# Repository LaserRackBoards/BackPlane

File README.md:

# BackPlane
19" 3U 84HP backplane used with Schroff subracks (might work with other brands also)

Fits 10pcs boards with 8HP front-panels and one board with 4HP panel (rightmost).

* connector: DIN41612, type C, 64 pins in rows a+c
* +15V/GND/-15V supply shared between all boards
* 17+17pin bus shared between all boards
* 2pins board-specific, all routed to slot-1 (J1, leftmost)

Backplane connector, Digikey 1195-1175-ND, Harting 09032646824, https://b2b.harting.com/09032646824

PCB RA connector, Digikey 1195-1149-ND, Harting 09031646921, https://b2b.harting.com/09036642921

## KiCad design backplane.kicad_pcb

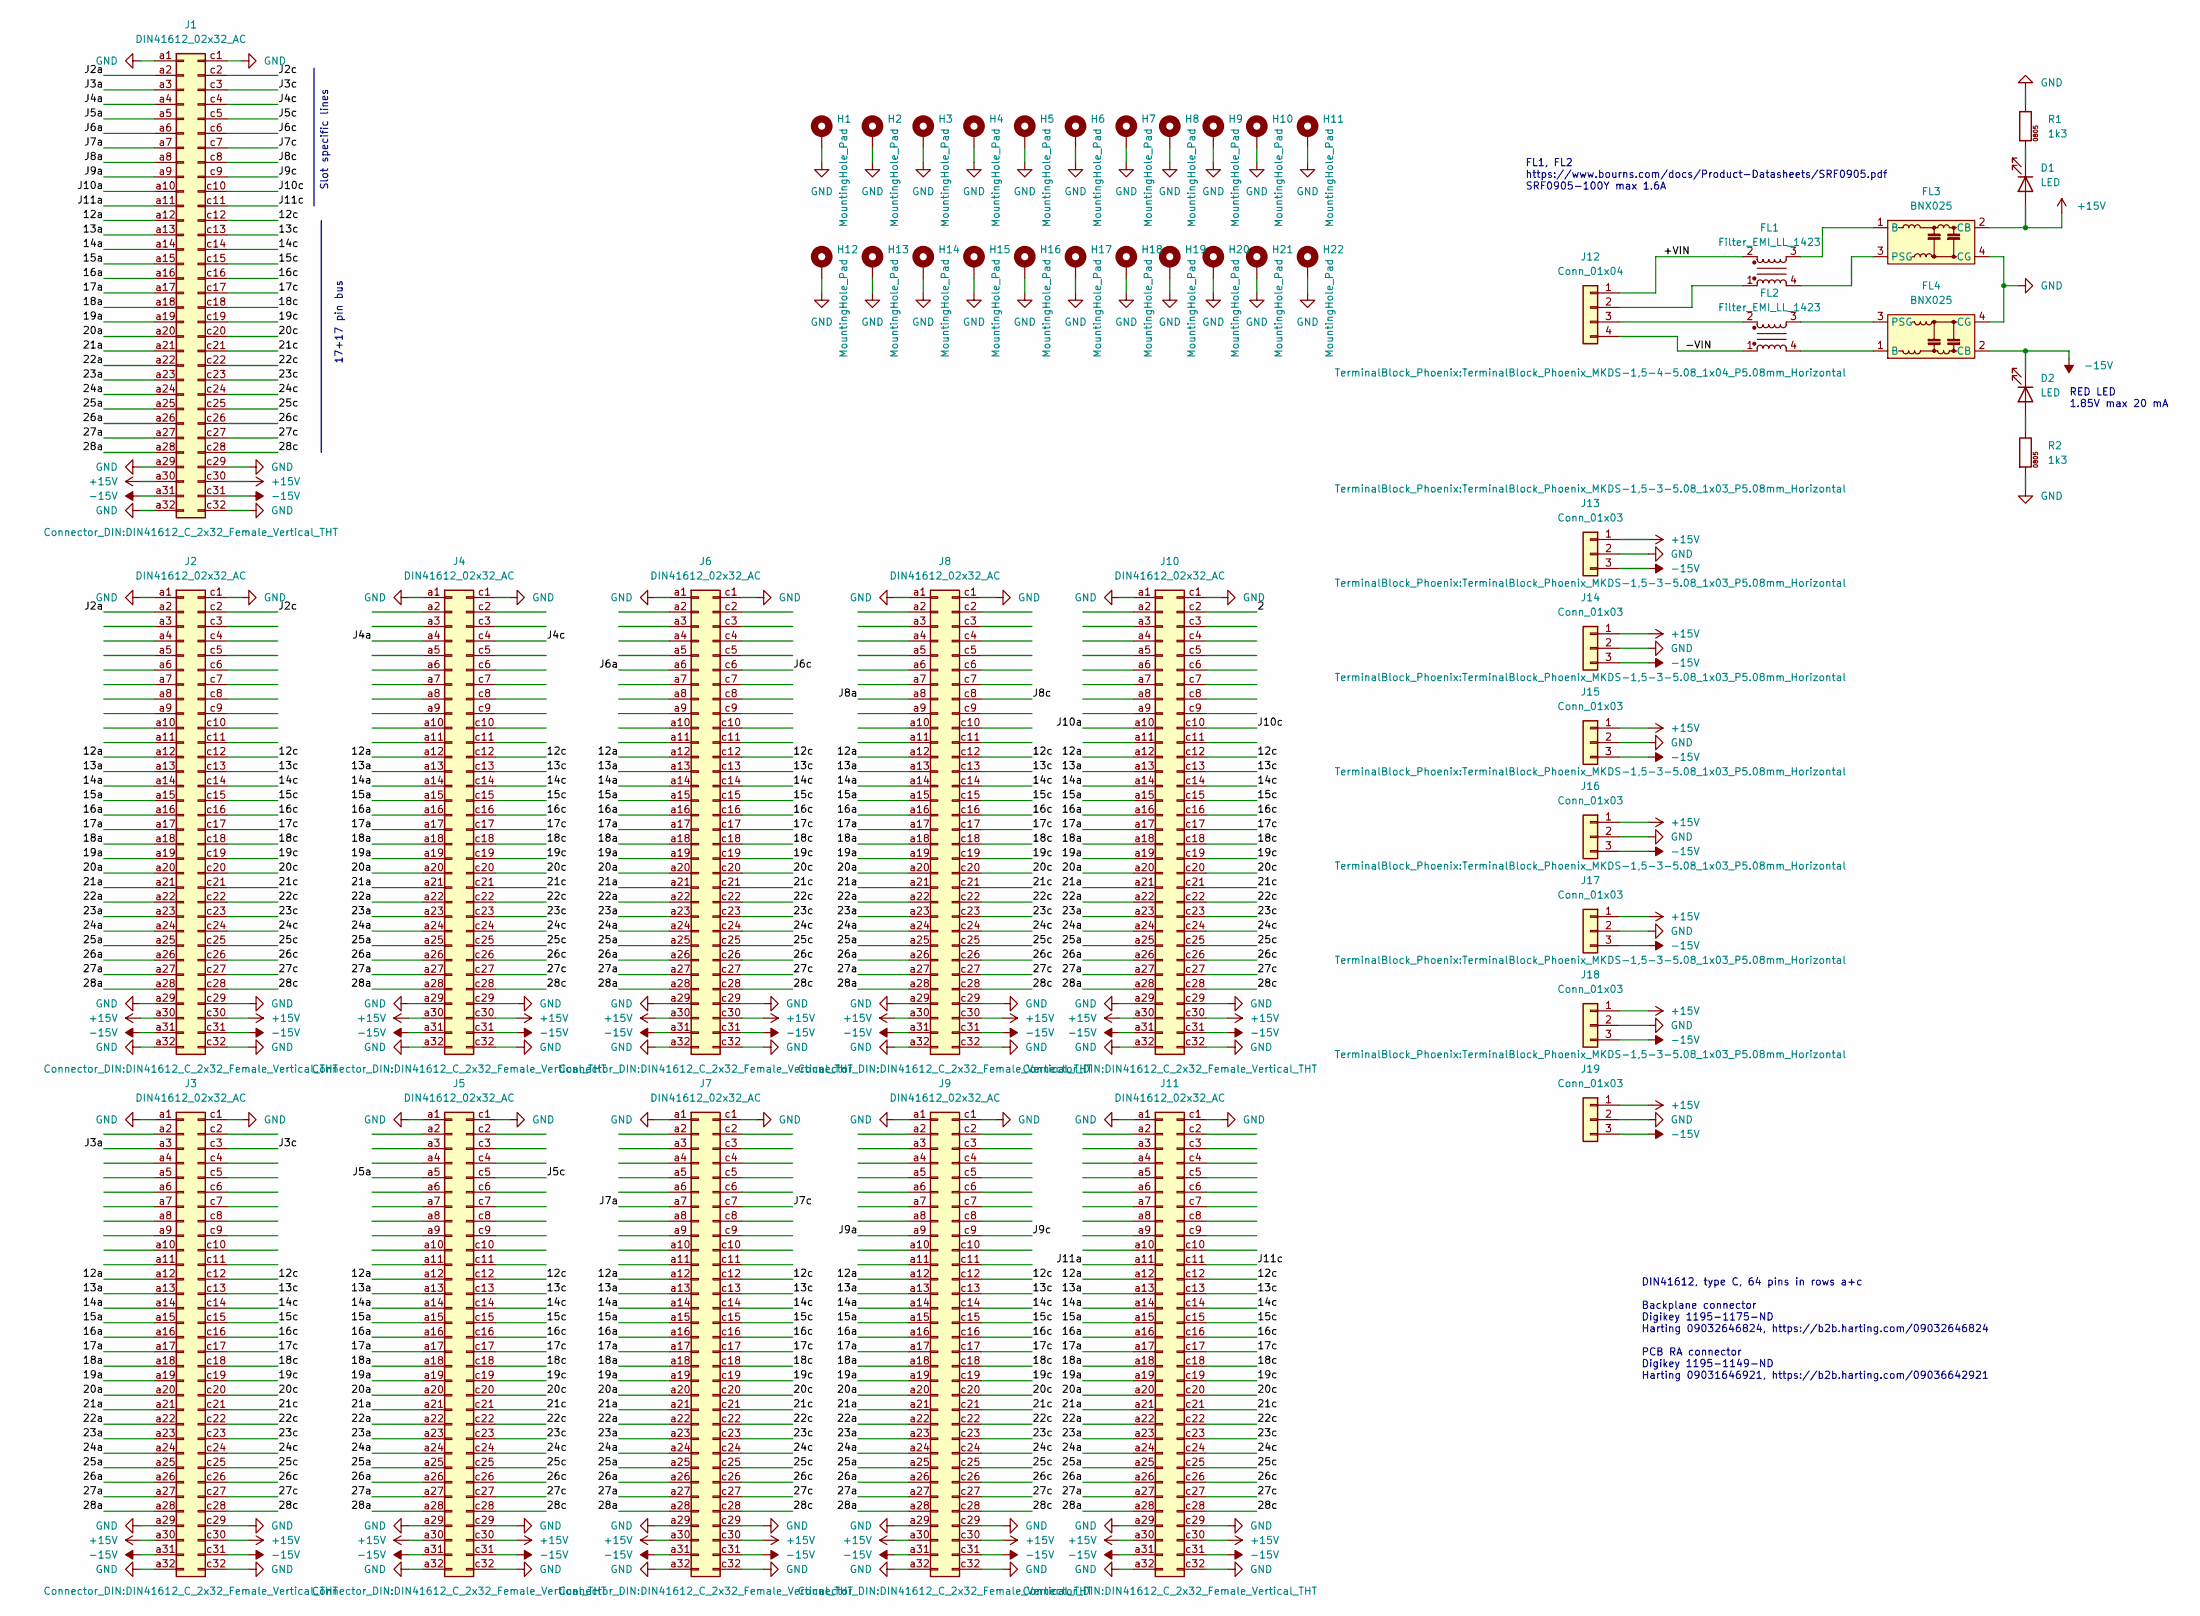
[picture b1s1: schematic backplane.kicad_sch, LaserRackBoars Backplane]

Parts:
D1, D2: LED; LED_0805_2012Metric
FL1, FL2: Filter_EMI_LL_1423; Filter_Bourns_SRF0905_6.0x9.2mm
FL3, FL4: BNX025; Filter_Murata_BNX025
H1, H2, H3, H4, H5, H6, H7, H8, H9, H10, H11, H12, H13, H14, H15, H16, H17, H18, H19, H20, H21, H22: MountingHole_Pad; MountingHole_2.7mm_M2.5_DIN965
J1, J2, J3, J4, J5, J6, J7, J8, J9, J10, J11: DIN41612_02x32_AC; DIN41612_C_2x32_Female_Vertical_THT
J12: Conn_01x04; TerminalBlock_Phoenix_MKDS-1,5-4-5.08_1x04_P5.08mm_Horizont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
J13, J14, J15, J16, J17, J18, J19: Conn_01x03; TerminalBlock_Phoenix_MKDS-1,5-3-5.08_1x03_P5.08mm_Horizont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
R1, R2: 1k3; R_0805_2012Metric

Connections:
+15V: D1.2 (A), FL3.2 (CB), J1.a30, J1.c30, J2.a30, J2.c30, J3.a30, J3.c30, J4.a30, J4.c30, J5.a30, J5.c30, J6.a30, J6.c30, J7.a30, J7.c30, J8.a30, J8.c30, J9.a30, J9.c30, J10.a30, J10.c30, J11.a30, J11.c30, J13.1, J14.1, J15.1, J16.1, J17.1, J18.1, J19.1
-15V: D2.1 (K), FL4.2 (CB), J1.a31, J1.c31, J2.a31, J2.c31, J3.a31, J3.c31, J4.a31, J4.c31, J5.a31, J5.c31, J6.a31, J6.c31, J7.a31, J7.c31, J8.a31, J8.c31, J9.a31, J9.c31, J10.a31, J10.c31, J11.a31, J11.c31, J13.3, J14.3, J15.3, J16.3, J17.3, J18.3, J19.3
/2: J10.c2
/12a: J1.a12, J2.a12, J3.a12, J4.a12, J5.a12, J6.a12, J7.a12, J8.a12, J9.a12, J10.a12, J11.a12
/12c: J1.c12, J2.c12, J3.c12, J4.c12, J5.c12, J6.c12, J7.c12, J8.c12, J9.c12, J10.c12, J11.c12
/13a: J1.a13, J2.a13, J3.a13, J4.a13, J5.a13, J6.a13, J7.a13, J8.a13, J9.a13, J10.a13, J11.a13
/13c: J1.c13, J2.c13, J3.c13, J4.c13, J5.c13, J6.c13, J7.c13, J8.c13, J9.c13, J10.c13, J11.c13
/14a: J1.a14, J2.a14, J3.a14, J4.a14, J5.a14, J6.a14, J7.a14, J8.a14, J9.a14, J10.a14, J11.a14
/14c: J1.c14, J2.c14, J3.c14, J4.c14, J5.c14, J6.c14, J7.c14, J8.c14, J9.c14, J10.c14, J11.c14
/15a: J1.a15, J2.a15, J3.a15, J4.a15, J5.a15, J6.a15, J7.a15, J8.a15, J9.a15, J10.a15, J11.a15
/15c: J1.c15, J2.c15, J3.c15, J4.c15, J5.c15, J6.c15, J7.c15, J8.c15, J9.c15, J10.c15, J11.c15
/16a: J1.a16, J2.a16, J3.a16, J4.a16, J5.a16, J6.a16, J7.a16, J8.a16, J9.a16, J10.a16, J11.a16
/16c: J1.c16, J2.c16, J3.c16, J4.c16, J5.c16, J6.c16, J7.c16, J8.c16, J9.c16, J10.c16, J11.c16
/17a: J1.a17, J2.a17, J3.a17, J4.a17, J5.a17, J6.a17, J7.a17, J8.a17, J9.a17, J10.a17, J11.a17
/17c: J1.c17, J2.c17, J3.c17, J4.c17, J5.c17, J6.c17, J7.c17, J8.c17, J9.c17, J10.c17, J11.c17
/18a: J1.a18, J2.a18, J3.a18, J4.a18, J5.a18, J6.a18, J7.a18, J8.a18, J9.a18, J10.a18, J11.a18
/18c: J1.c18, J2.c18, J3.c18, J4.c18, J5.c18, J6.c18, J7.c18, J8.c18, J9.c18, J10.c18, J11.c18
/19a: J1.a19, J2.a19, J3.a19, J4.a19, J5.a19, J6.a19, J7.a19, J8.a19, J9.a19, J10.a19, J11.a19
/19c: J1.c19, J2.c19, J3.c19, J4.c19, J5.c19, J6.c19, J7.c19, J8.c19, J9.c19, J10.c19, J11.c19
/20a: J1.a20, J2.a20, J3.a20, J4.a20, J5.a20, J6.a20, J7.a20, J8.a20, J9.a20, J10.a20, J11.a20
/20c: J1.c20, J2.c20, J3.c20, J4.c20, J5.c20, J6.c20, J7.c20, J8.c20, J9.c20, J10.c20, J11.c20
/21a: J1.a21, J2.a21, J3.a21, J4.a21, J5.a21, J6.a21, J7.a21, J8.a21, J9.a21, J10.a21, J11.a21
/21c: J1.c21, J2.c21, J3.c21, J4.c21, J5.c21, J6.c21, J7.c21, J8.c21, J9.c21, J10.c21, J11.c21
/22a: J1.a22, J2.a22, J3.a22, J4.a22, J5.a22, J6.a22, J7.a22, J8.a22, J9.a22, J10.a22, J11.a22
/22c: J1.c22, J2.c22, J3.c22, J4.c22, J5.c22, J6.c22, J7.c22, J8.c22, J9.c22, J10.c22, J11.c22
/23a: J1.a23, J2.a23, J3.a23, J4.a23, J5.a23, J6.a23, J7.a23, J8.a23, J9.a23, J10.a23, J11.a23
/23c: J1.c23, J2.c23, J3.c23, J4.c23, J5.c23, J6.c23, J7.c23, J8.c23, J9.c23, J10.c23, J11.c23
/24a: J1.a24, J2.a24, J3.a24, J4.a24, J5.a24, J6.a24, J7.a24, J8.a24, J9.a24, J10.a24, J11.a24
/24c: J1.c24, J2.c24, J3.c24, J4.c24, J5.c24, J6.c24, J7.c24, J8.c24, J9.c24, J10.c24, J11.c24
/25a: J1.a25, J2.a25, J3.a25, J4.a25, J5.a25, J6.a25, J7.a25, J8.a25, J9.a25, J10.a25, J11.a25
/25c: J1.c25, J2.c25, J3.c25, J4.c25, J5.c25, J6.c25, J7.c25, J8.c25, J9.c25, J10.c25, J11.c25
/26a: J1.a26, J2.a26, J3.a26, J4.a26, J5.a26, J6.a26, J7.a26, J8.a26, J9.a26, J10.a26, J11.a26
/26c: J1.c26, J2.c26, J3.c26, J4.c26, J5.c26, J6.c26, J7.c26, J8.c26, J9.c26, J10.c26, J11.c26
/27a: J1.a27, J2.a27, J3.a27, J4.a27, J5.a27, J6.a27, J7.a27, J8.a27, J9.a27, J10.a27, J11.a27
/27c: J1.c27, J2.c27, J3.c27, J4.c27, J5.c27, J6.c27, J7.c27, J8.c27, J9.c27, J10.c27, J11.c27
/28a: J1.a28, J2.a28, J3.a28, J4.a28, J5.a28, J6.a28, J7.a28, J8.a28, J9.a28, J10.a28, J11.a28
/28c: J1.c28, J2.c28, J3.c28, J4.c28, J5.c28, J6.c28, J7.c28, J8.c28, J9.c28, J10.c28, J11.c28
/+VIN: FL1.2, J12.1
/-VIN: FL2.1, J12.4
/J2a: J1.a2, J2.a2
/J2c: J1.c2, J2.c2
/J3a: J1.a3, J3.a3
/J3c: J1.c3, J3.c3
/J4a: J1.a4, J4.a4
/J4c: J1.c4, J4.c4
/J5a: J1.a5, J5.a5
/J5c: J1.c5, J5.c5
/J6a: J1.a6, J6.a6
/J6c: J1.c6, J6.c6
/J7a: J1.a7, J7.a7
/J7c: J1.c7, J7.c7
/J8a: J1.a8, J8.a8
/J8c: J1.c8, J8.c8
/J9a: J1.a9, J9.a9
/J9c: J1.c9, J9.c9
/J10a: J1.a10, J10.a10
/J10c: J1.c10, J10.c10
/J11a: J1.a11, J11.a11
/J11c: J1.c11, J11.c11
GND: FL3.4 (CG), FL4.4 (CG), H1.1, H2.1, H3.1, H4.1, H5.1, H6.1, H7.1, H8.1, H9.1, H10.1, H11.1, H12.1, H13.1, H14.1, H15.1, H16.1, H17.1, H18.1, H19.1, H20.1, H21.1, H22.1, J1.a1, J1.a29, J1.a32, J1.c1, J1.c29, J1.c32, J2.a1, J2.a29, J2.a32, J2.c1, J2.c29, J2.c32, J3.a1, J3.a29, J3.a32, J3.c1, J3.c29, J3.c32, J4.a1, J4.a29, J4.a32, J4.c1, J4.c29, J4.c32, J5.a1, J5.a29, J5.a32, J5.c1, J5.c29, J5.c32, J6.a1, J6.a29, J6.a32, J6.c1, J6.c29, J6.c32, J7.a1, J7.a29, J7.a32, J7.c1, J7.c29, J7.c32, J8.a1, J8.a29, J8.a32, J8.c1, J8.c29, J8.c32, J9.a1, J9.a29, J9.a32, J9.c1, J9.c29, J9.c32, J10.a1, J10.a29, J10.a32, J10.c1, J10.c29, J10.c32, J11.a1, J11.a29, J11.a32, J11.c1, J11.c29, J11.c32, J13.2, J14.2, J15.2, J16.2, J17.2, J18.2, J19.2, R1.1, R2.2
unnamed: D1.1 (K), R1.2
unnamed: D2.2 (A), R2.1
unnamed: FL1.1, J12.2
unnamed: FL1.3, FL3.1 (B)
unnamed: FL1.4, FL3.3 (PSG)
unnamed: FL2.2, J12.3
unnamed: FL2.3, FL4.3 (PSG)
unnamed: FL2.4, FL4.1 (B)

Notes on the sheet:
DIN41612, type C, 64 pins in rows a+c Backplane connector Digikey 1195-1175-ND Harting 09032646824, https://b2b.harting.com/09032646824 PCB RA connector Digikey 1195-1149-ND Harting 09031646921, https://b2b.harting.com/09036642921
RED LED 1.85V max 20 mA
17+17 pin bus
Slot specific lines
FL1, FL2 https://www.bourns.com/docs/Product-Datasheets/SRF0905.pdf SRF0905-100Y max 1.6A

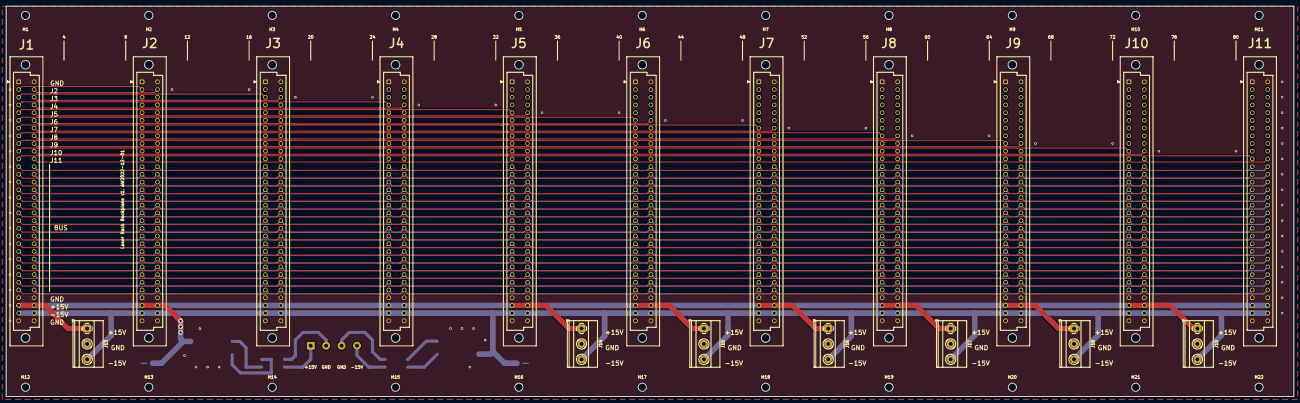
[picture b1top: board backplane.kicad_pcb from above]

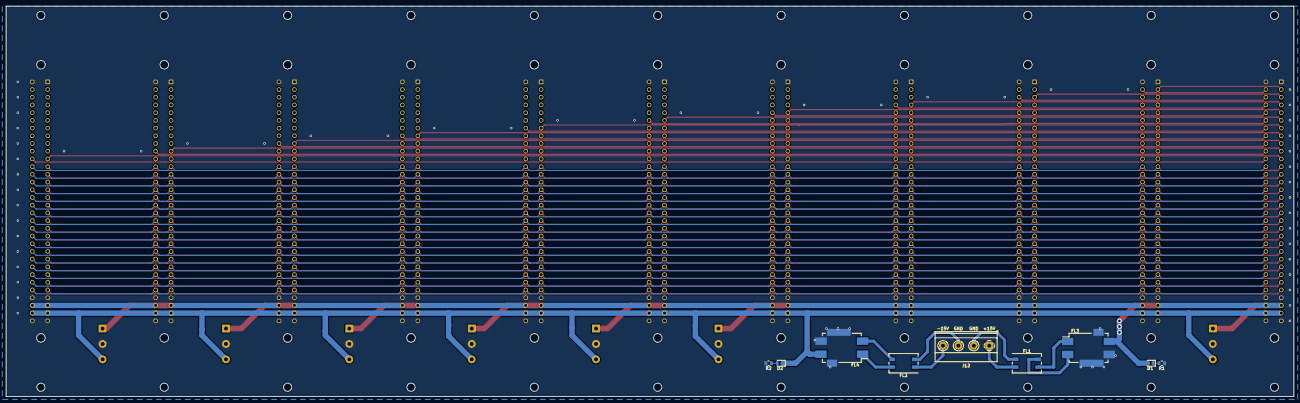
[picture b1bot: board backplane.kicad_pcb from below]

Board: 2 copper layers, 424.2 x 128.6 mm, 49 parts (9 on the bottom side), 67 nets.

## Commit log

2026-04-06 kicad 10
